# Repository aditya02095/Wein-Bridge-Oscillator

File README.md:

# Wein-Bridge-Oscillator
Created a PCB file for the Wein Bridge Oscillator created

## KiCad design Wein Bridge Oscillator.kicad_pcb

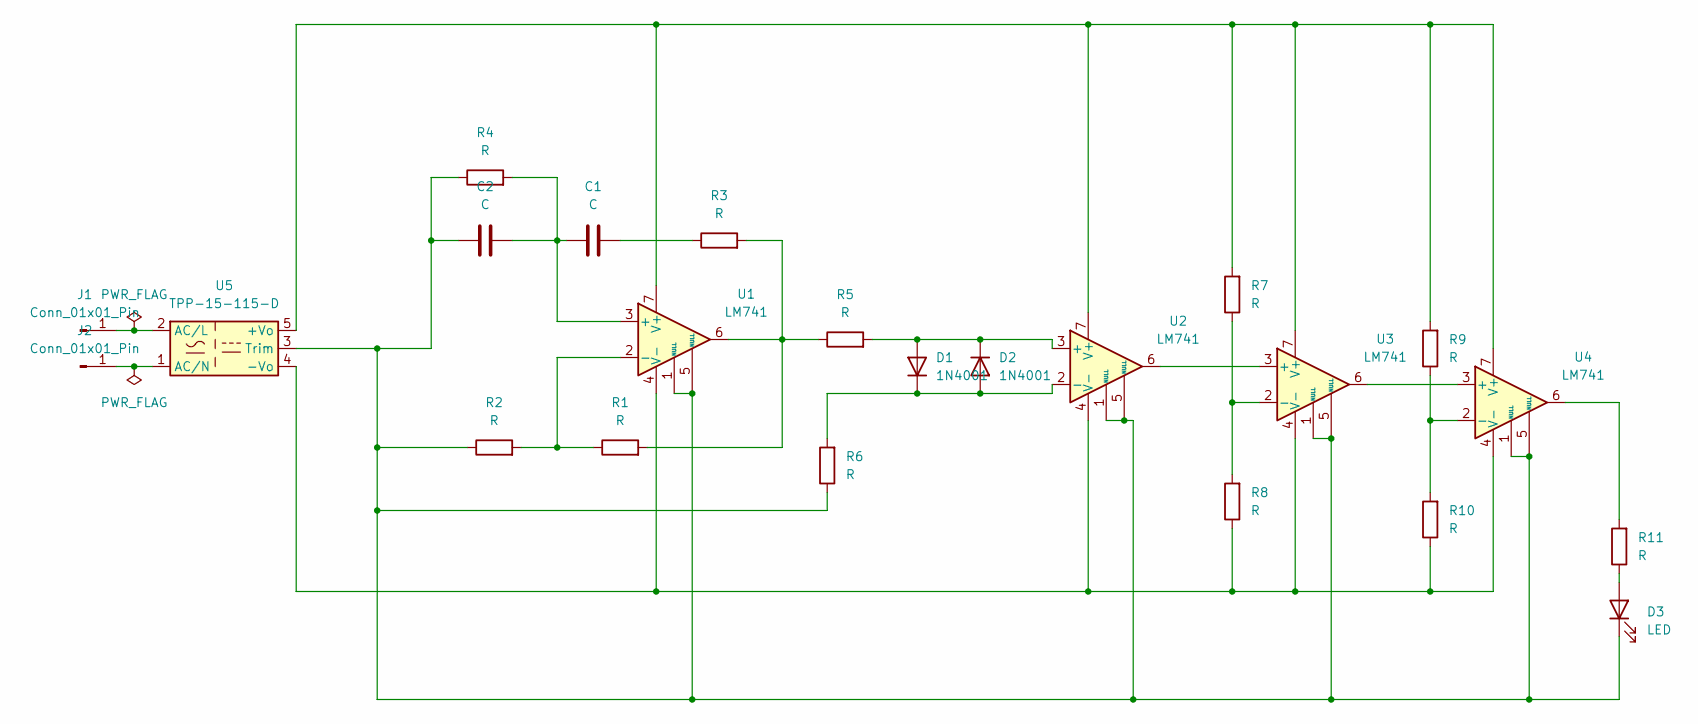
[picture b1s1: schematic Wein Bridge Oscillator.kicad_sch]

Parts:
C1, C2: C; CP_Elec_3x5.4
D1, D2: 1N4001; D_DO-41_SOD81_P10.16mm_Horizontal
D3: LED; LED_0805_2012Metric_Pad1.15x1.40mm_HandSolder
J1, J2: Conn_01x01_Pin; Pin_D0.7mm_L6.5mm_W1.8mm_FlatFork
R1, R2, R3, R4, R5, R6, R7, R8, R9, R10, R11: R; R_0402_1005Metric_Pad0.72x0.64mm_HandSolder
U1, U2, U3, U4: LM741; OpAmp_741
U5: TPP-15-115-D; Converter_ACDC_TRACO_TPP-15-1xx-D_THT

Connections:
unnamed: C1.2, R3.1
unnamed: D1.2 (A), D2.1 (K), R5.2, U2.3 (+)
unnamed: D1.1 (K), D2.2 (A), R6.2, U2.2 (-)
unnamed: D3.2 (A), R11.1
unnamed: C2.1, D3.1 (K), R2.1, R4.1, R6.1, U1.1 (NULL), U1.5 (NULL), U2.1 (NULL), U2.5 (NULL), U3.1 (NULL), U3.5 (NULL), U4.1 (NULL), U4.5 (NULL), U5.3 (Trim)
unnamed: J1.1 (Pin_1_1), U5.2 (AC/L)
unnamed: J2.1 (Pin_1_1), U5.1 (AC/N)
unnamed: R1.2, R3.2, R5.1, U1.6
unnamed: R11.2, U4.6
unnamed: C1.1, C2.2, R4.2, U1.3 (+)
unnamed: R1.1, R2.2, U1.2 (-)
unnamed: R7.2, R9.2, U1.7 (V+), U2.7 (V+), U3.7 (V+), U4.7 (V+), U5.5 (+Vo)
unnamed: R8.1, R10.1, U1.4 (V-), U2.4 (V-), U3.4 (V-), U4.4 (V-), U5.4 (-Vo)
unnamed: U2.6, U3.3 (+)
unnamed: R7.1, R8.2, U3.2 (-)
unnamed: U3.6, U4.3 (+)
unnamed: R9.1, R10.2, U4.2 (-)

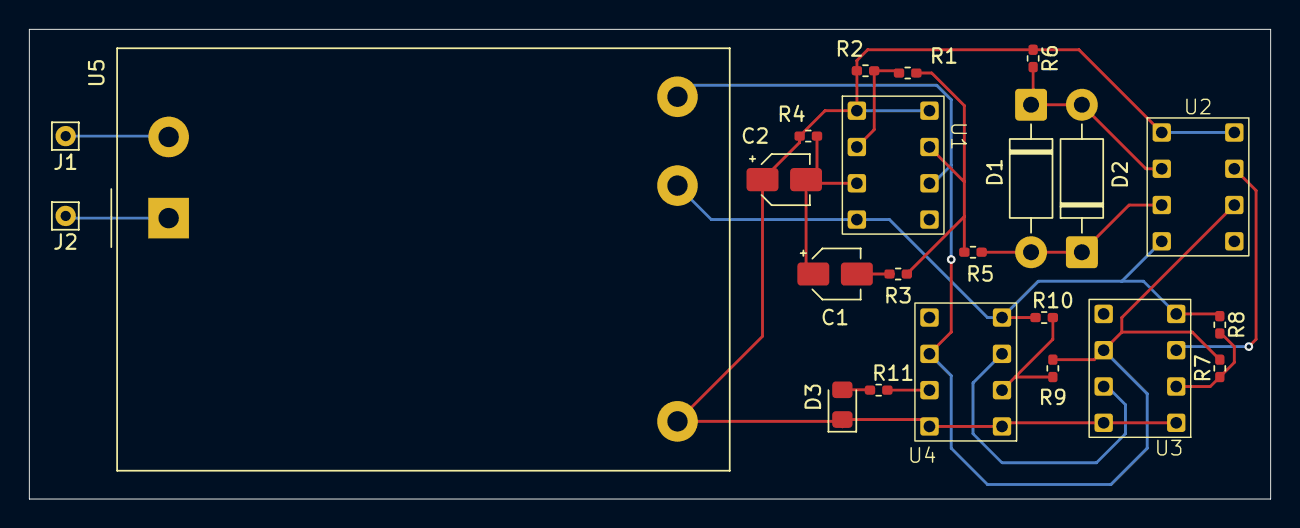
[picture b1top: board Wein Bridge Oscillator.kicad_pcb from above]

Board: 2 copper layers, 85.5 x 32.3 mm, 23 parts (0 on the bottom side), 17 nets.
